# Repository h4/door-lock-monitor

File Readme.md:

# Door Lock Monitor

## Schemas

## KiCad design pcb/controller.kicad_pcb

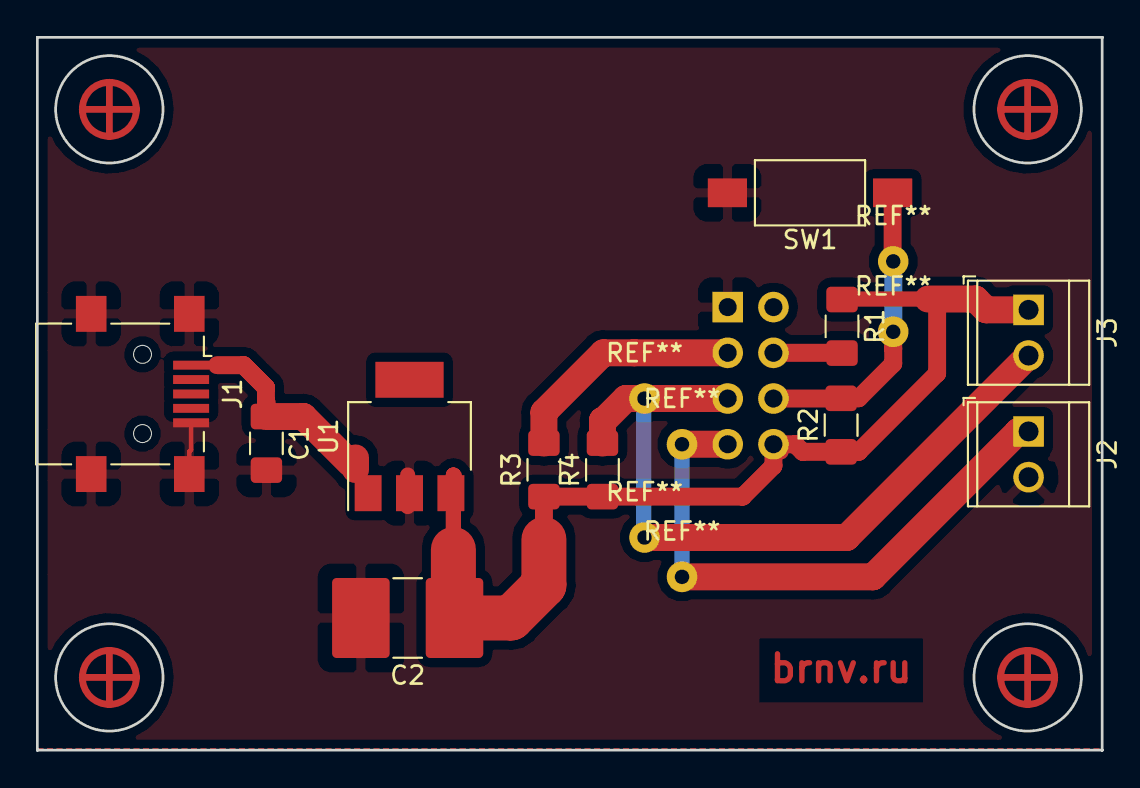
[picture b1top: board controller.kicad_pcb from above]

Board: 2 copper layers, 59.2 x 39.6 mm, 12 parts (1 on the bottom side), 8 nets.

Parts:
C1: C0.1mF; C_1206_3216Metric_Pad1.42x1.75mm_HandSolder
C2: CP10mF; C_2816_7142Metric_Pad3.20x4.45mm_HandSolder
J1: USB_B_Mini; USB_Mini-B_Lumberg_2486_01_Horizontal
J2, J3: Screw_Terminal_01x02; TerminalBlock_TE_282834-2_1x02_P2.54mm_Horizontal
R1, R2, R3, R4: R10k; R_1206_3216Metric_Pad1.42x1.75mm_HandSolder
SW1: SW_Push; SW_SPST_FSMSM
U1: LM2937xS; SOT-223
U2: ESP-01v090; PinSocket_2x04_P2.54mm_Vertical_Flip

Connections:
+5V: C1.1, J1.1, U1.1
/board_out_gnd: J3.2, R4.2, U2.6
/board_out_vcc: C2.1, J3.1, R1.1, R2.1, R3.1, R4.1, U1.3, U2.7
/sw_out: J2.1, U2.8
Earth: C1.2, C2.2, J1.5, J1.6, J2.2, SW1.2, U1.2, U2.2
unnamed: R1.2, U2.3
unnamed: R2.2, SW1.1, U2.5
unnamed: R3.2, U2.4

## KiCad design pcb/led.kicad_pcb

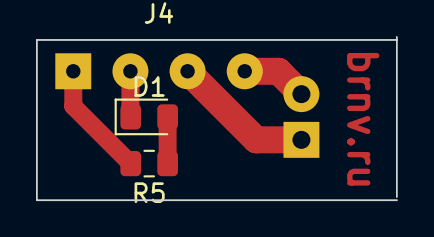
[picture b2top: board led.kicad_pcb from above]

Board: 2 copper layers, 20.0 x 9.1 mm, 4 parts (1 on the bottom side), 5 nets.

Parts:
D1: LED; LED_0805_2012Metric_Pad1.15x1.40mm_HandSolder
J4: Conn_01x02; SolderWirePad_1x04_P3.175mm_Drill0.8mm
J5: Conn_01x02; PinHeader_1x02_P2.54mm_Horizontal
R5: 68R; R_0805_2012Metric_Pad1.15x1.40mm_HandSolder

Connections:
/led_in: J4.1, R5.2
/led_out: D1.1, J4.2
/sw_in: J4.3, J5.1
/sw_out: J4.4, J5.2
unnamed: D1.2, R5.1

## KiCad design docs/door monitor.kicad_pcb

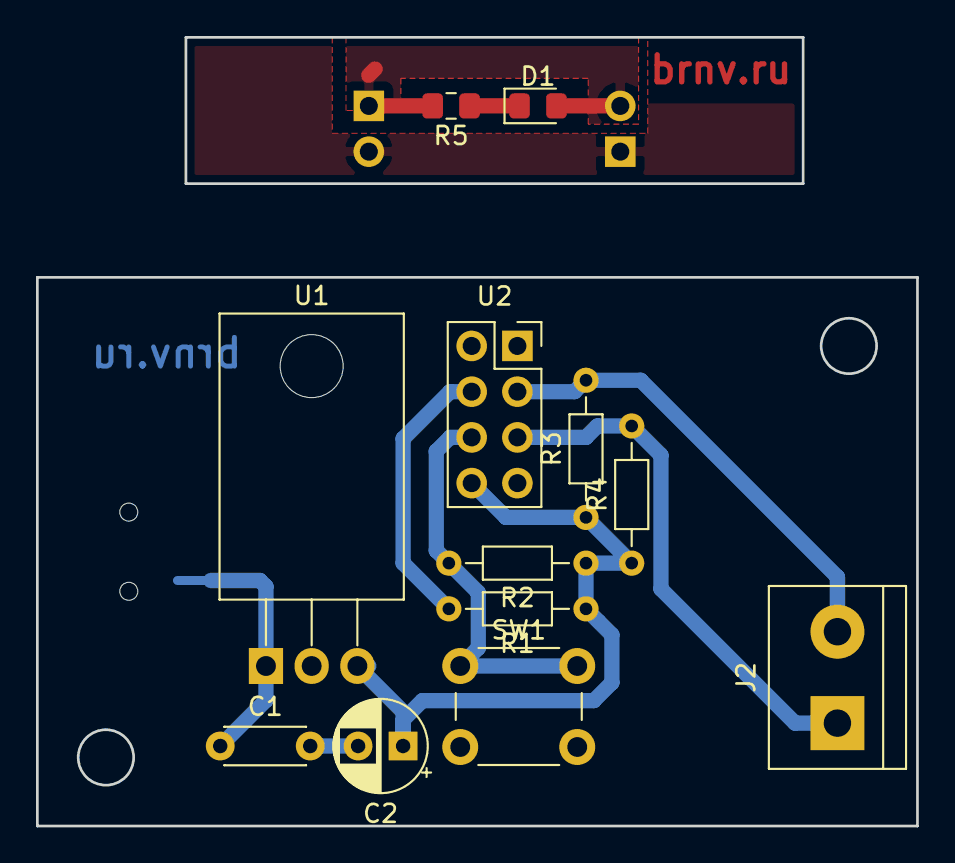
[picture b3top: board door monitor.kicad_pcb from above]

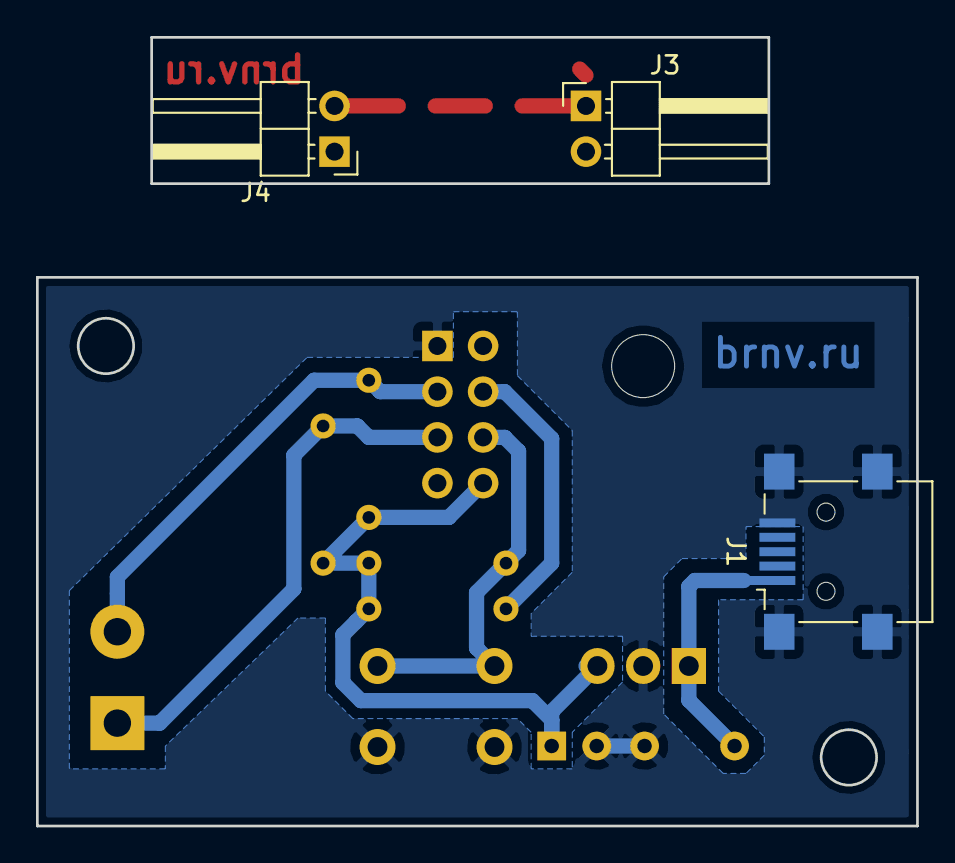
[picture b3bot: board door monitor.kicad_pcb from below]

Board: 2 copper layers, 48.9 x 43.8 mm, 15 parts (3 on the bottom side), 10 nets.

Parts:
C1: C0.1mF; C_Disc_D4.3mm_W1.9mm_P5.00mm
C2: CP10mF; CP_Radial_D5.0mm_P2.50mm
D1: LED; LED_0805_2012Metric_Pad1.15x1.40mm_HandSolder
J1: USB_B_Mini; USB_Mini-B_Lumberg_2486_01_Horizontal
J2: Screw_Terminal_01x02; TerminalBlock_bornier-2_P5.08mm
J3, J4: Conn_01x02_Male; PinHeader_1x02_P2.54mm_Horizontal
R1, R2, R3, R4: R10k; R_Axial_DIN0204_L3.6mm_D1.6mm_P7.62mm_Horizontal
R5: R; R_0805_2012Metric_Pad1.15x1.40mm_HandSolder
SW1: SW_Push; SW_PUSH_6mm_H5mm
U1: LM2937xS; TO-220-3_Horizontal_TabDown
U2: ESP-01v090; PinSocket_2x04_P2.54mm_Vertical_Flip

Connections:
+5V: C1.1, J1.1, U1.1
Earth: C1.2, C2.2, J1.5, J1.6, SW1.2, U1.2, U2.2
unnamed: C2.1, R1.1, R2.1, R3.1, R4.1, U1.3, U2.7
unnamed: D1.1, R5.1
unnamed: D1.2, J3.1, J4.2, R5.2
unnamed: J2.1, R3.2, U2.4
unnamed: J2.2, R4.2, U2.6
unnamed: J3.2, J4.1
unnamed: R1.2, U2.3
unnamed: R2.2, SW1.1, U2.5

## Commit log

2018-09-09 Support MQTT messaging
2018-09-09 Set correct topic names
2018-09-14 Add docs
2018-09-17 Move to kicad
2018-09-17 Increase track space on PCB
2018-09-18 Update pcb
2018-10-04 Update electrical shema
2018-11-04 Add LED signal and update PCB
2018-11-13 Run ESP in client only mode
